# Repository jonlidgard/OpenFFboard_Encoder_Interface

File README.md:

## OpenFFBoard Motor Encoder Interface

See <https://github.com/Ultrawipf>

This board connects to the encoder interface pins on the TMC board.
There is a provision on the PCB to run from either 5v or 3.3V.

Probably the pull-up resistors, filter caps & inline resistors are
no longer required on the TMC board.

If running from 3.3V then the level shifters on the TMC board are not
required either. These will need to have solder bridges across the
relevant pins.

Produced with [Kicad 5.1](https://www.kicad.org)

### Version History
V1.0  - 14/04/20  - Initial release.

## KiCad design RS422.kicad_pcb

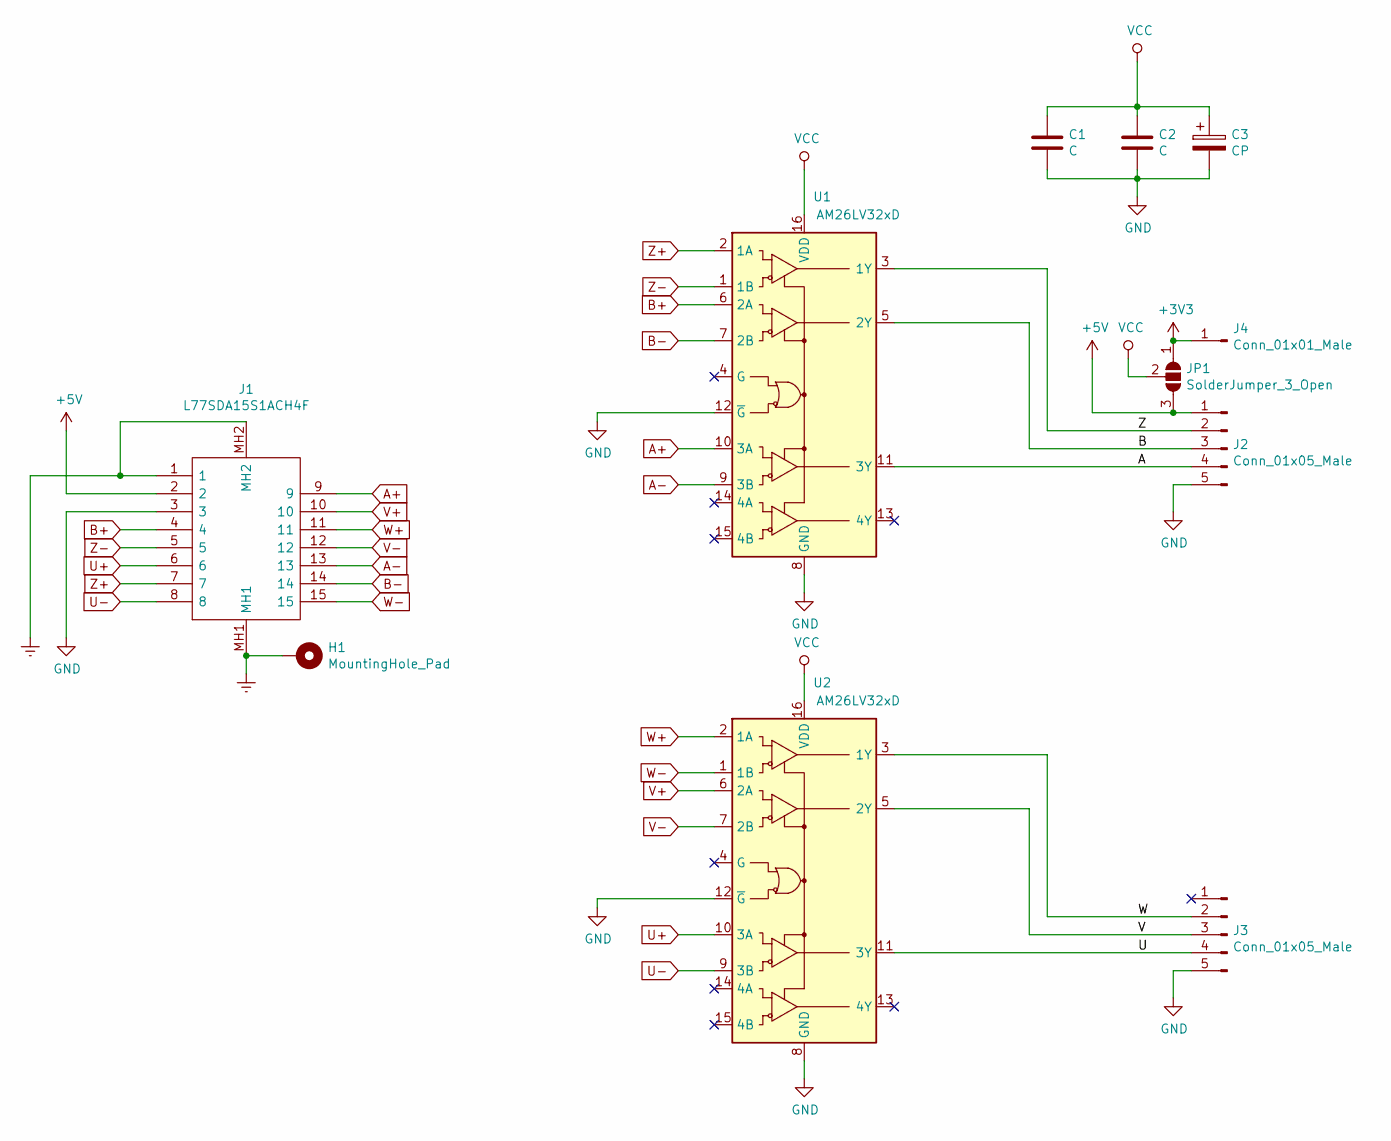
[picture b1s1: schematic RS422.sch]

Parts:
C1, C2: C; C_1206_HandSoldering
C3: CP; CP_Elec_4x5.3
H1: MountingHole_Pad; MountingHole_3.2mm_M3_Pad
J1: L77SDA15S1ACH4F; Manufacturer_Part_Number L77SDA15S1ACH4F
J2, J3: Conn_01x05_Male; Pin_Header_Straight_1x05_Pitch2.54mm
J4: Conn_01x01_Male; Pin_Header_Straight_1x01_Pitch2.54mm
JP1: SolderJumper_3_Open; GS3
U1, U2: AM26LV32xD; AM26C32CD

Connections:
+3V3: J4.1, JP1.1 (A)
+5V: J1.2, J2.1, JP1.3 (B)
/A: J2.4, U1.11 (3Y)
/B: J2.3, U1.5 (2Y)
/U: J3.4, U2.11 (3Y)
/V: J3.3, U2.5 (2Y)
/W: J3.2, U2.3 (1Y)
/Z: J2.2, U1.3 (1Y)
A+: J1.9, U1.10 (3A)
A-: J1.13, U1.9 (3B)
B+: J1.4, U1.6 (2A)
B-: J1.14, U1.7 (2B)
Earth: H1.1, J1.1, J1.MH1, J1.MH2
GND: C1.2, C2.2, C3.2, J1.3, J2.5, J3.5, U1.8 (GND), U1.12 (~G), U2.8 (GND), U2.12 (~G)
U+: J1.6, U2.10 (3A)
U-: J1.8, U2.9 (3B)
V+: J1.10, U2.6 (2A)
V-: J1.12, U2.7 (2B)
VCC: C1.1, C2.1, C3.1, JP1.2 (C), U1.16 (VDD), U2.16 (VDD)
W+: J1.11, U2.2 (1A)
W-: J1.15, U2.1 (1B)
Z+: J1.7, U1.2 (1A)
Z-: J1.5, U1.1 (1B)

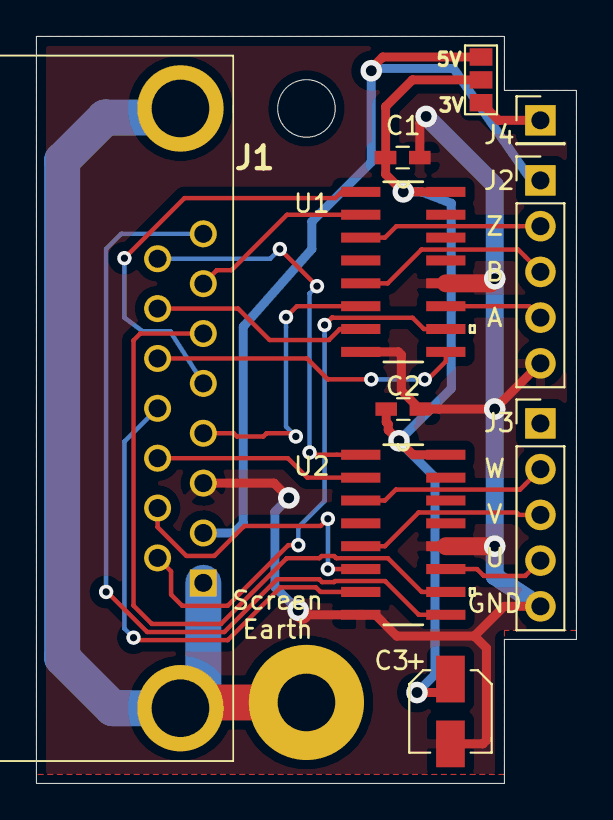
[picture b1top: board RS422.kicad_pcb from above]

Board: 2 copper layers, 30.0 x 41.5 mm, 11 parts (0 on the bottom side), 23 nets.

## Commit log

2020-04-14 Updated README & Silkscreen mods
2020-04-14 Moved Gerbers
2020-04-14 Clean up ignored files
2020-04-16 Added Mige encoder cable colors
2021-11-10 Update README.md
    https://forum.kicad.info/t/warning-avoid-all-links-to-kicad-pcb-org-use-kicad-org/31521

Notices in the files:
parts and their libraries:
Copyright 2016 Accelerated Designs. All rights reserved.
